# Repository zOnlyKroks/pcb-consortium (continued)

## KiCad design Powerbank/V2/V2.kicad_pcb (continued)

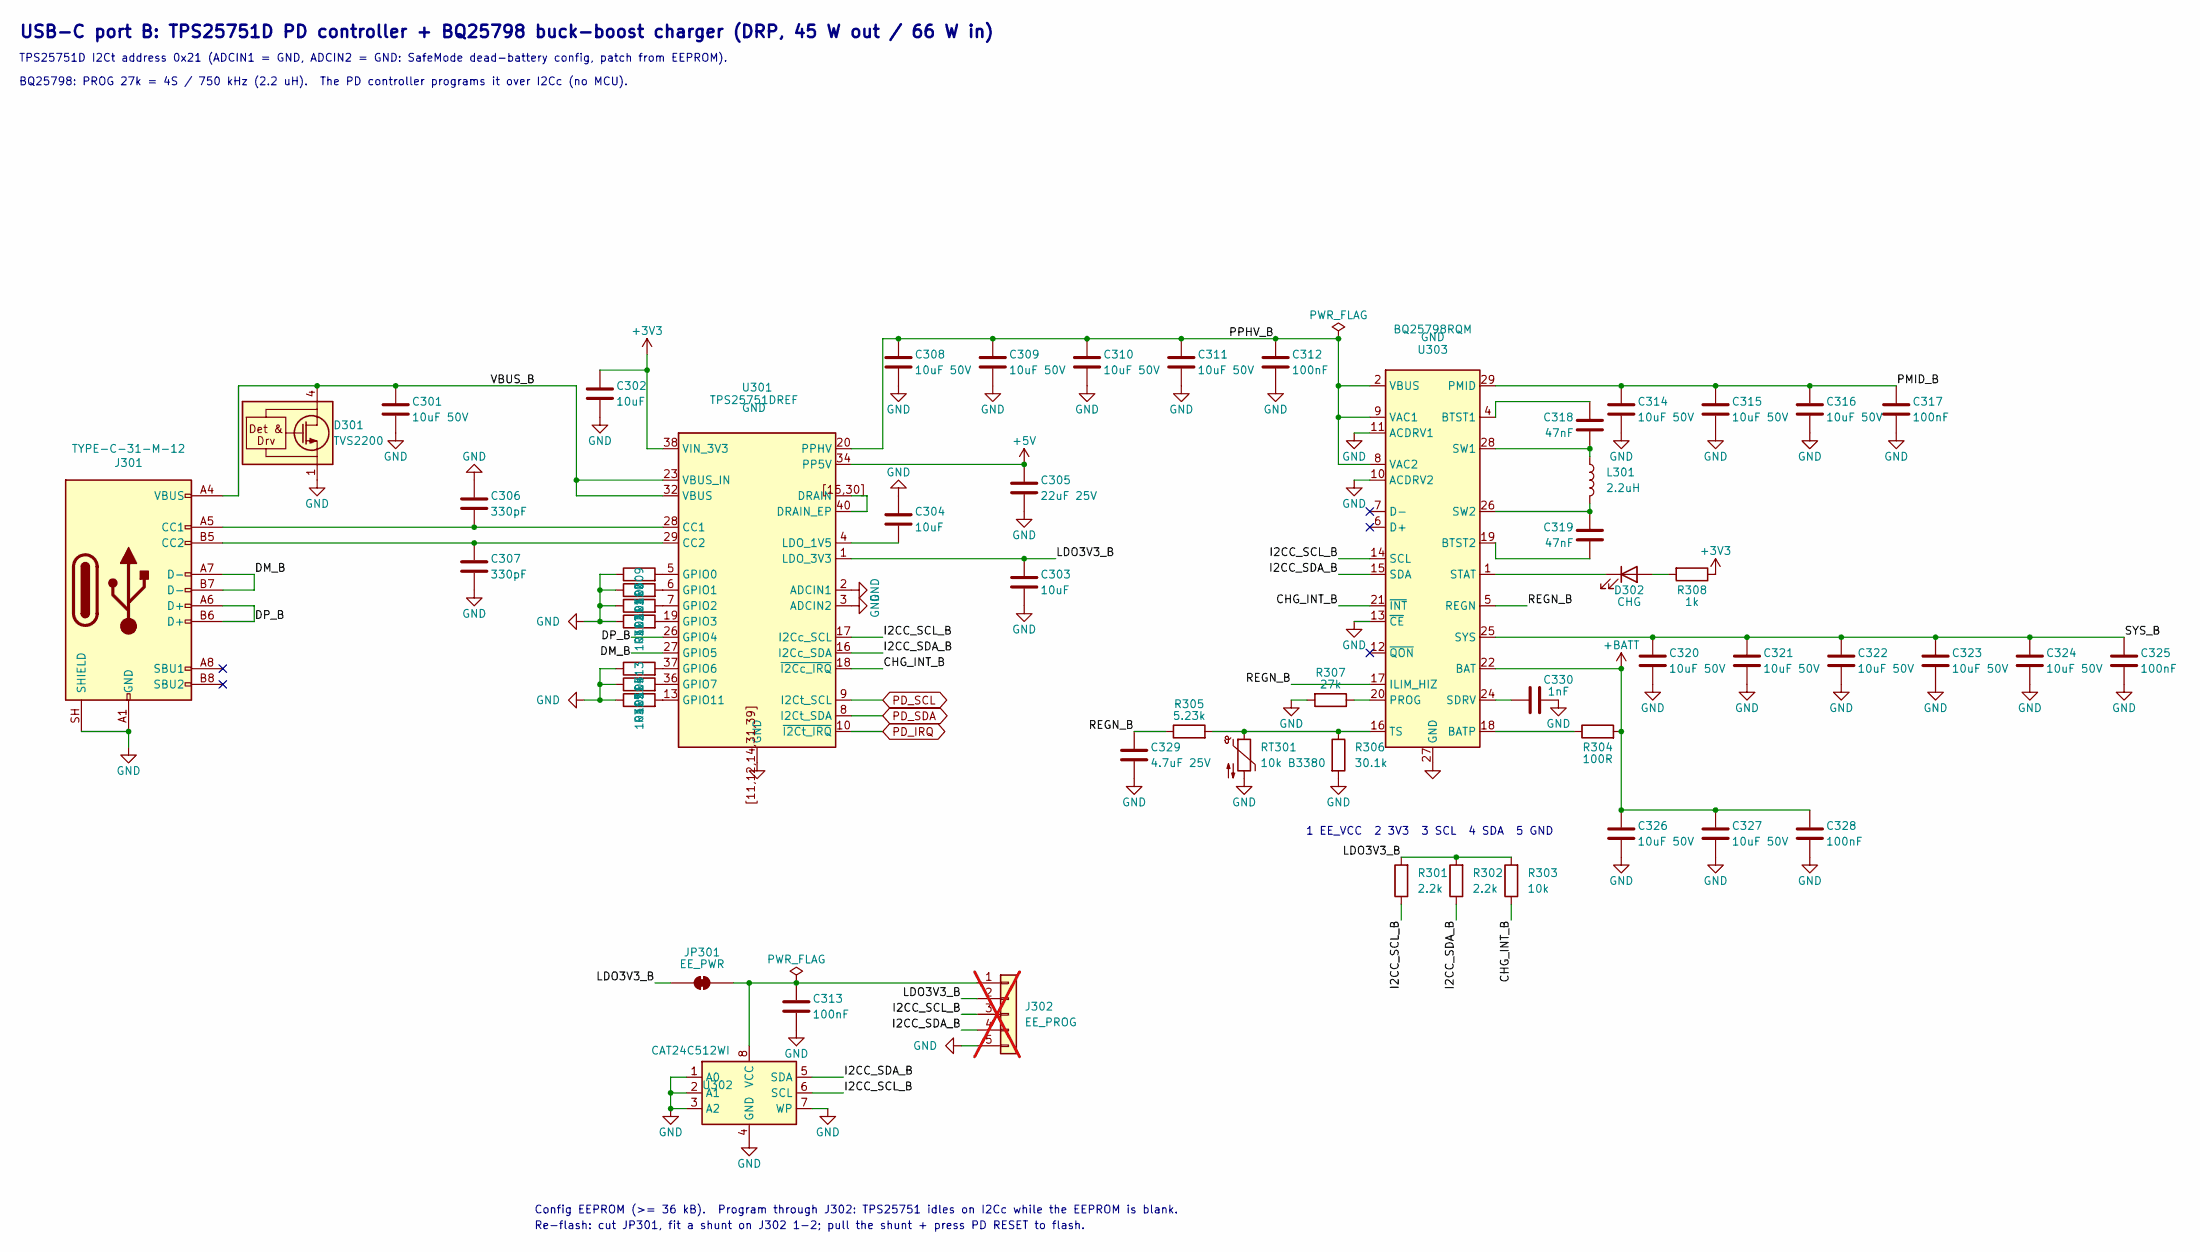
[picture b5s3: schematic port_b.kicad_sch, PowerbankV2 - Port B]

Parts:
C301, C308, C309, C310, C311, C314, C315, C316, C320, C321, C322, C323, C324, C326, C327: 10uF 50V; C_1206_3216Metric; LCSC Part # C13585
C302, C303, C304: 10uF; C_0603_1608Metric; LCSC Part # C19702
C305: 22uF 25V; C_0805_2012Metric; LCSC Part # C45783
C306, C307: 330pF; C_0603_1608Metric; LCSC Part # C1664
C312, C313, C317, C325, C328: 100nF; C_0603_1608Metric; LCSC Part # C14663
C318, C319: 47nF; C_0603_1608Metric; LCSC Part # C1622
C329: 4.7uF 25V; C_0805_2012Metric; LCSC Part # C1779
C330: 1nF; C_0603_1608Metric; LCSC Part # C1588
D301: TVS2200; WSON-6-1EP_2x2mm_P0.65mm_EP1x1.6mm; LCSC Part # C523793
D302: CHG; LED_0603_1608Metric; LCSC Part # C2286
J301: TYPE-C-31-M-12; USB_C_Receptacle_HRO_TYPE-C-31-M-12; LCSC Part # C165948
J302: EE_PROG; PinHeader_1x05_P2.54mm_Vertical; not fitted
JP301: EE_PWR; SolderJumper-2_P1.3mm_Bridged_RoundedPad1.0x1.5mm
L301: 2.2uH; L_7.0x6.6_MWSA0603S; LCSC Part # C408445
R301, R302: 2.2k; R_0603_1608Metric; LCSC Part # C4190
R303, R309, R310, R311, R312, R313, R314, R315: 10k; R_0603_1608Metric; LCSC Part # C25804
R304: 100R; R_0603_1608Metric; LCSC Part # C22775
R305: 5.23k; R_0603_1608Metric; LCSC Part # C23068
R306: 30.1k; R_0603_1608Metric; LCSC Part # C23000
R307: 27k; R_0603_1608Metric; LCSC Part # C22967
R308: 1k; R_0603_1608Metric; LCSC Part # C21190
RT301: 10k B3380; R_0603_1608Metric; LCSC Part # C13564
U301: TPS25751DREF; Texas_REF0038A_WQFN-38-2EP_6x4mm_P0.4_Via0.3; LCSC Part # C30169739
U302: CAT24C512WI; SOIC-8_3.9x4.9mm_P1.27mm; LCSC Part # C79986
U303: BQ25798RQM; Texas_RQM0029A_VQFN-29_4x4mm_P0.4mm; LCSC Part # C2876593

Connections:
+3V3: C302.1, R308.1, U301.38 (VIN_3V3); also elsewhere on the board
+5V: C305.1, U301.34 (PP5V); also elsewhere on the board
+BATT: C326.1, C327.1, C328.1, R304.2, U303.22 (BAT), U303.23 (BAT); also elsewhere on the board
/Port B/CHG_INT_B: R303.1, U301.18 (~I2Cc_IRQ), U303.21 (~INT)
/Port B/DM_B: J301.A7 (D-), J301.B7 (D-), U301.27 (GPIO5)
/Port B/DP_B: J301.A6 (D+), J301.B6 (D+), U301.26 (GPIO4)
/Port B/I2CC_SCL_B: J302.3, R301.1, U301.17 (I2Cc_SCL), U302.6 (SCL), U303.14 (SCL)
/Port B/I2CC_SDA_B: J302.4, R302.1, U301.16 (I2Cc_SDA), U302.5 (SDA), U303.15 (SDA)
/Port B/LDO3V3_B: C303.1, J302.2, JP301.1 (A), R301.2, R302.2, R303.2, U301.1 (LDO_3V3)
/Port B/PMID_B: C314.1, C315.1, C316.1, C317.1, U303.29 (PMID)
/Port B/PPHV_B: C308.1, C309.1, C310.1, C311.1, C312.1, U301.20 (PPHV), U303.2 (VBUS), U303.3 (VBUS), U303.8 (VAC2), U303.9 (VAC1)
/Port B/REGN_B: C329.1, R305.1, U303.5 (REGN), U303.17 (ILIM_HIZ)
/Port B/SYS_B: C320.1, C321.1, C322.1, C323.1, C324.1, C325.1, U303.25 (SYS)
/Port B/VBUS_B: C301.1, D301.4 (IN), D301.5 (IN), D301.6 (IN), J301.A4 (VBUS), J301.A9 (VBUS), J301.B4 (VBUS), J301.B9 (VBUS), U301.23 (VBUS_IN), U301.32 (VBUS)
GND: C301.2, C302.2, C303.2, C304.2, C305.2, C306.2, C307.2, C308.2, C309.2, C310.2, C311.2, C312.2, C313.2, C314.2, C315.2, C316.2, C317.2, C320.2, C321.2, C322.2, C323.2, C324.2, C325.2, C326.2, C327.2, C328.2, C329.2, C330.2, D301.1 (GND), D301.2 (GND), D301.3 (GND), D301.7 (GND), J301.A1 (GND), J301.A12 (GND), J301.B1 (GND), J301.B12 (GND), J301.SH (SHIELD), J302.5, R306.2, R307.2, R309.1, R310.1, R311.1, R312.1, R313.1, R314.1, R315.1, RT301.2, U301.2 (ADCIN1), U301.3 (ADCIN2), U301.11, U301.12, U301.14, U301.31, U301.39, U301.[11,12,14,31,39] (GND), U302.1 (A0), U302.2 (A1), U302.3 (A2), U302.4 (GND), U302.7 (WP), U303.10 (ACDRV2), U303.11 (ACDRV1), U303.13 (~CE), U303.27 (GND); also elsewhere on the board
unnamed: D302.2 (A), R308.2
unnamed: D302.1 (K), U303.1 (STAT)
unnamed: C306.1, J301.A5 (CC1), U301.28 (CC1)
unnamed: C307.1, J301.B5 (CC2), U301.29 (CC2)
unnamed: C313.1, J302.1, JP301.2 (B), U302.8 (VCC)
unnamed: U301.15, U301.30, U301.40 (DRAIN_EP), U301.[15,30] (DRAIN)
unnamed: R309.2, U301.5 (GPIO0)
unnamed: R310.2, U301.6 (GPIO1)
unnamed: R311.2, U301.7 (GPIO2)
unnamed: R312.2, U301.19 (GPIO3)
unnamed: R313.2, U301.37 (GPIO6)
unnamed: R314.2, U301.36 (GPIO7)
unnamed: R315.2, U301.13 (GPIO11)
unnamed: C304.1, U301.4 (LDO_1V5)
unnamed: R304.1, U303.18 (BATP)
unnamed: C318.1, U303.4 (BTST1)
unnamed: C319.1, U303.19 (BTST2)
unnamed: R307.1, U303.20 (PROG)
unnamed: C330.1, U303.24 (SDRV)
unnamed: C318.2, L301.1, U303.28 (SW1)
unnamed: C319.2, L301.2, U303.26 (SW2)
unnamed: R305.2, R306.1, RT301.1, U303.16 (TS)
PD_IRQ: U301.10 (~I2Ct_IRQ); also elsewhere on the board
PD_SCL: U301.9 (I2Ct_SCL); also elsewhere on the board
PD_SDA: U301.8 (I2Ct_SDA); also elsewhere on the board

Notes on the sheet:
Re-flash: cut JP301, fit a shunt on J302 1-2; pull the shunt + press PD RESET to flash.
1 EE_VCC 2 3V3 3 SCL 4 SDA 5 GND
USB-C port B: TPS25751D PD controller + BQ25798 buck-boost charger (DRP, 45 W out / 66 W in)
TPS25751D I2Ct address 0x21 (ADCIN1 = GND, ADCIN2 = GND: SafeMode dead-battery config, patch from EEPROM).
Config EEPROM (>= 36 kB). Program through J302: TPS25751 idles on I2Cc while the EEPROM is blank.
BQ25798: PROG 27k = 4S / 750 kHz (2.2 uH). The PD controller programs it over I2Cc (no MCU).

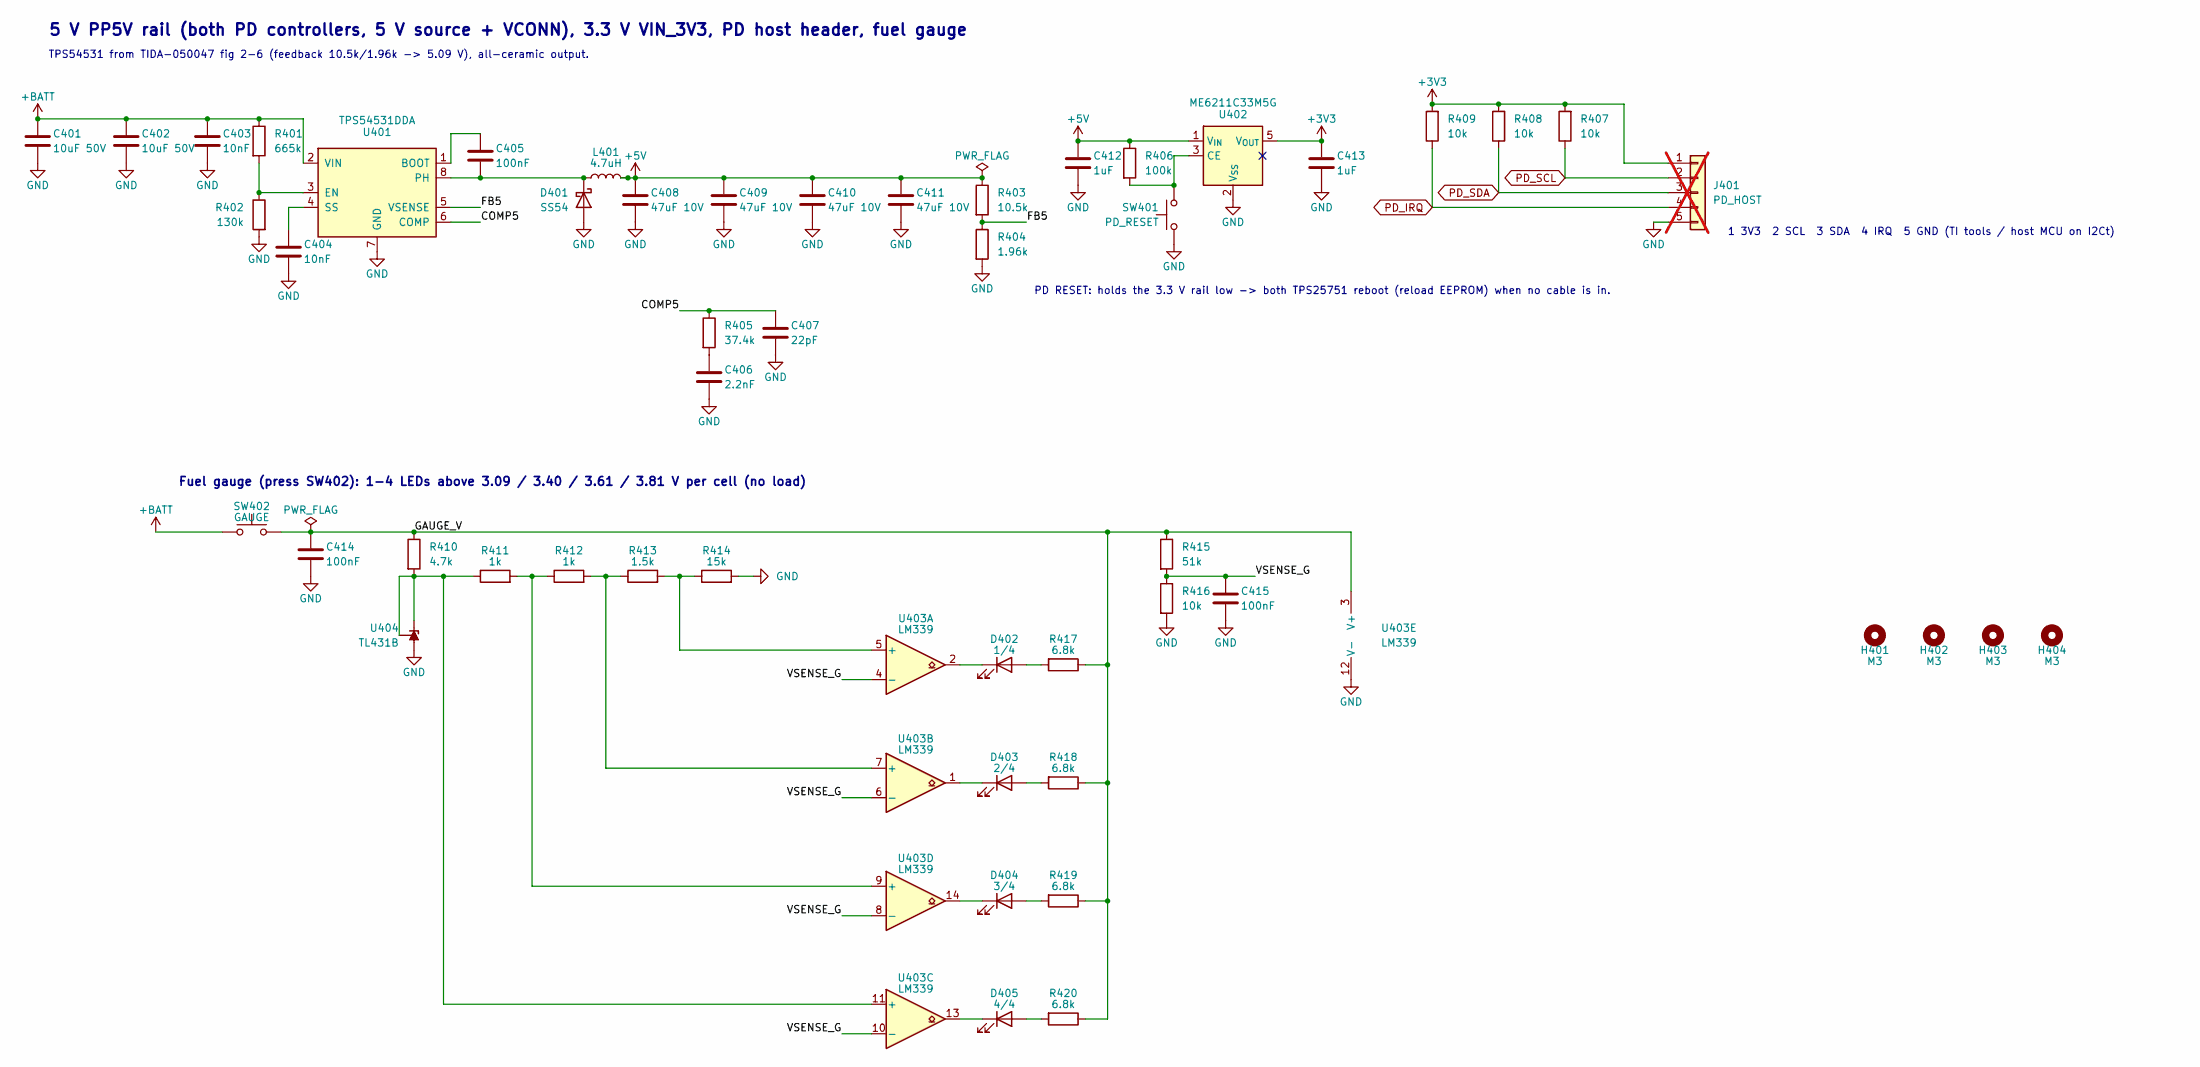
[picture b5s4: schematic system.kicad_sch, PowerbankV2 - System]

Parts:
C401, C402: 10uF 50V; C_1206_3216Metric; LCSC Part # C13585
C403, C404: 10nF; C_0603_1608Metric; LCSC Part # C57112
C405, C414, C415: 100nF; C_0603_1608Metric; LCSC Part # C14663
C406: 2.2nF; C_0603_1608Metric; LCSC Part # C1604
C407: 22pF; C_0603_1608Metric; LCSC Part # C1653
C408, C409, C410, C411: 47uF 10V; C_1206_3216Metric; LCSC Part # C96123
C412, C413: 1uF; C_0603_1608Metric; LCSC Part # C15849
D401: SS54; D_SMA; LCSC Part # C22452
D402: 1/4; LED_0603_1608Metric; LCSC Part # C2290
D403: 2/4; LED_0603_1608Metric; LCSC Part # C2290
D404: 3/4; LED_0603_1608Metric; LCSC Part # C2290
D405: 4/4; LED_0603_1608Metric; LCSC Part # C2290
H401, H402, H403, H404: M3; MountingHole_3.2mm_M3
J401: PD_HOST; PinHeader_1x05_P2.54mm_Vertical; not fitted
L401: 4.7uH; L_11x10_TMPA1004S; LCSC Part # C357112
R401: 665k; R_0603_1608Metric; LCSC Part # C23227
R402: 130k; R_0603_1608Metric; LCSC Part # C22795
R403: 10.5k; R_0603_1608Metric; LCSC Part # C22855
R404: 1.96k; R_0603_1608Metric; LCSC Part # C22854
R405: 37.4k; R_0603_1608Metric; LCSC Part # C23033
R406: 100k; R_0603_1608Metric; LCSC Part # C25803
R407, R408, R409, R416: 10k; R_0603_1608Metric; LCSC Part # C25804
R410: 4.7k; R_0603_1608Metric; LCSC Part # C23162
R411, R412: 1k; R_0603_1608Metric; LCSC Part # C21190
R413: 1.5k; R_0603_1608Metric; LCSC Part # C22843
R414: 15k; R_0603_1608Metric; LCSC Part # C22809
R415: 51k; R_0603_1608Metric; LCSC Part # C23196
R417, R418, R419, R420: 6.8k; R_0603_1608Metric; LCSC Part # C23212
SW401: PD_RESET; SW_TS-1187A_5.1x5.1; LCSC Part # C318884
SW402: GAUGE; SW_TS-1187A_5.1x5.1; LCSC Part # C318884
U401: TPS54531DDA; TI_SO-PowerPAD-8_ThermalVias; LCSC Part # C50605
U402: ME6211C33M5G; SOT-23-5; LCSC Part # C82942
U403: LM339; SOIC-14_3.9x8.7mm_P1.27mm; LCSC Part # C7948
U404: TL431B; SOT-23; LCSC Part # C41283

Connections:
+3V3: C413.1, J401.1, R407.2, R408.2, R409.2, U402.5 (V_{OUT}); also elsewhere on the board
+5V: C408.1, C409.1, C410.1, C411.1, C412.1, L401.2, R403.1, R406.1, U402.1 (V_{IN}); also elsewhere on the board
+BATT: C401.1, C402.1, C403.1, R401.1, SW402.1, U401.2 (VIN); also elsewhere on the board
/System/COMP5: C407.1, R405.1, U401.6 (COMP)
/System/FB5: R403.2, R404.1, U401.5 (VSENSE)
/System/GAUGE_V: C414.1, R410.1, R415.1, R417.1, R418.1, R419.1, R420.1, SW402.4 (2), U403.3 (V+)
/System/VSENSE_G: C415.1, R415.2, R416.1, U403.4 (-), U403.6 (-), U403.8 (-), U403.10 (-)
GND: C401.2, C402.2, C403.2, C404.2, C406.2, C407.2, C408.2, C409.2, C410.2, C411.2, C412.2, C413.2, C414.2, C415.2, D401.2 (A), J401.5, R402.2, R404.2, R414.2, R416.2, SW401.4 (2), U401.7 (GND), U401.9 (PAD), U402.2 (V_{SS}), U403.12 (V-), U404.3 (A); also elsewhere on the board
unnamed: C406.1, R405.2
unnamed: C405.2, D401.1 (K), L401.1, U401.8 (PH)
unnamed: D402.2 (A), R417.2
unnamed: D402.1 (K), U403.2
unnamed: D403.2 (A), R418.2
unnamed: D403.1 (K), U403.1
unnamed: D404.2 (A), R419.2
unnamed: D404.1 (K), U403.14
unnamed: D405.2 (A), R420.2
unnamed: D405.1 (K), U403.13
unnamed: C405.1, U401.1 (BOOT)
unnamed: R401.2, R402.1, U401.3 (EN)
unnamed: C404.1, U401.4 (SS)
unnamed: R406.2, SW401.1, U402.3 (CE)
unnamed: R413.2, R414.1, U403.5 (+)
unnamed: R412.2, R413.1, U403.7 (+)
unnamed: R410.2, R411.1, U403.11 (+), U404.1 (K), U404.2 (REF)
unnamed: R411.2, R412.1, U403.9 (+)
PD_IRQ: J401.4, R409.1; also elsewhere on the board
PD_SCL: J401.2, R407.1; also elsewhere on the board
PD_SDA: J401.3, R408.1; also elsewhere on the board

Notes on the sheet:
5 V PP5V rail (both PD controllers, 5 V source + VCONN), 3.3 V VIN_3V3, PD host header, fuel gauge
TPS54531 from TIDA-050047 fig 2-6 (feedback 10.5k/1.96k -> 5.09 V), all-ceramic output.
Fuel gauge (press SW402): 1-4 LEDs above 3.09 / 3.40 / 3.61 / 3.81 V per cell (no load)
PD RESET: holds the 3.3 V rail low -> both TPS25751 reboot (reload EEPROM) when no cable is in.
1 3V3 2 SCL 3 SDA 4 IRQ 5 GND (TI tools / host MCU on I2Ct)

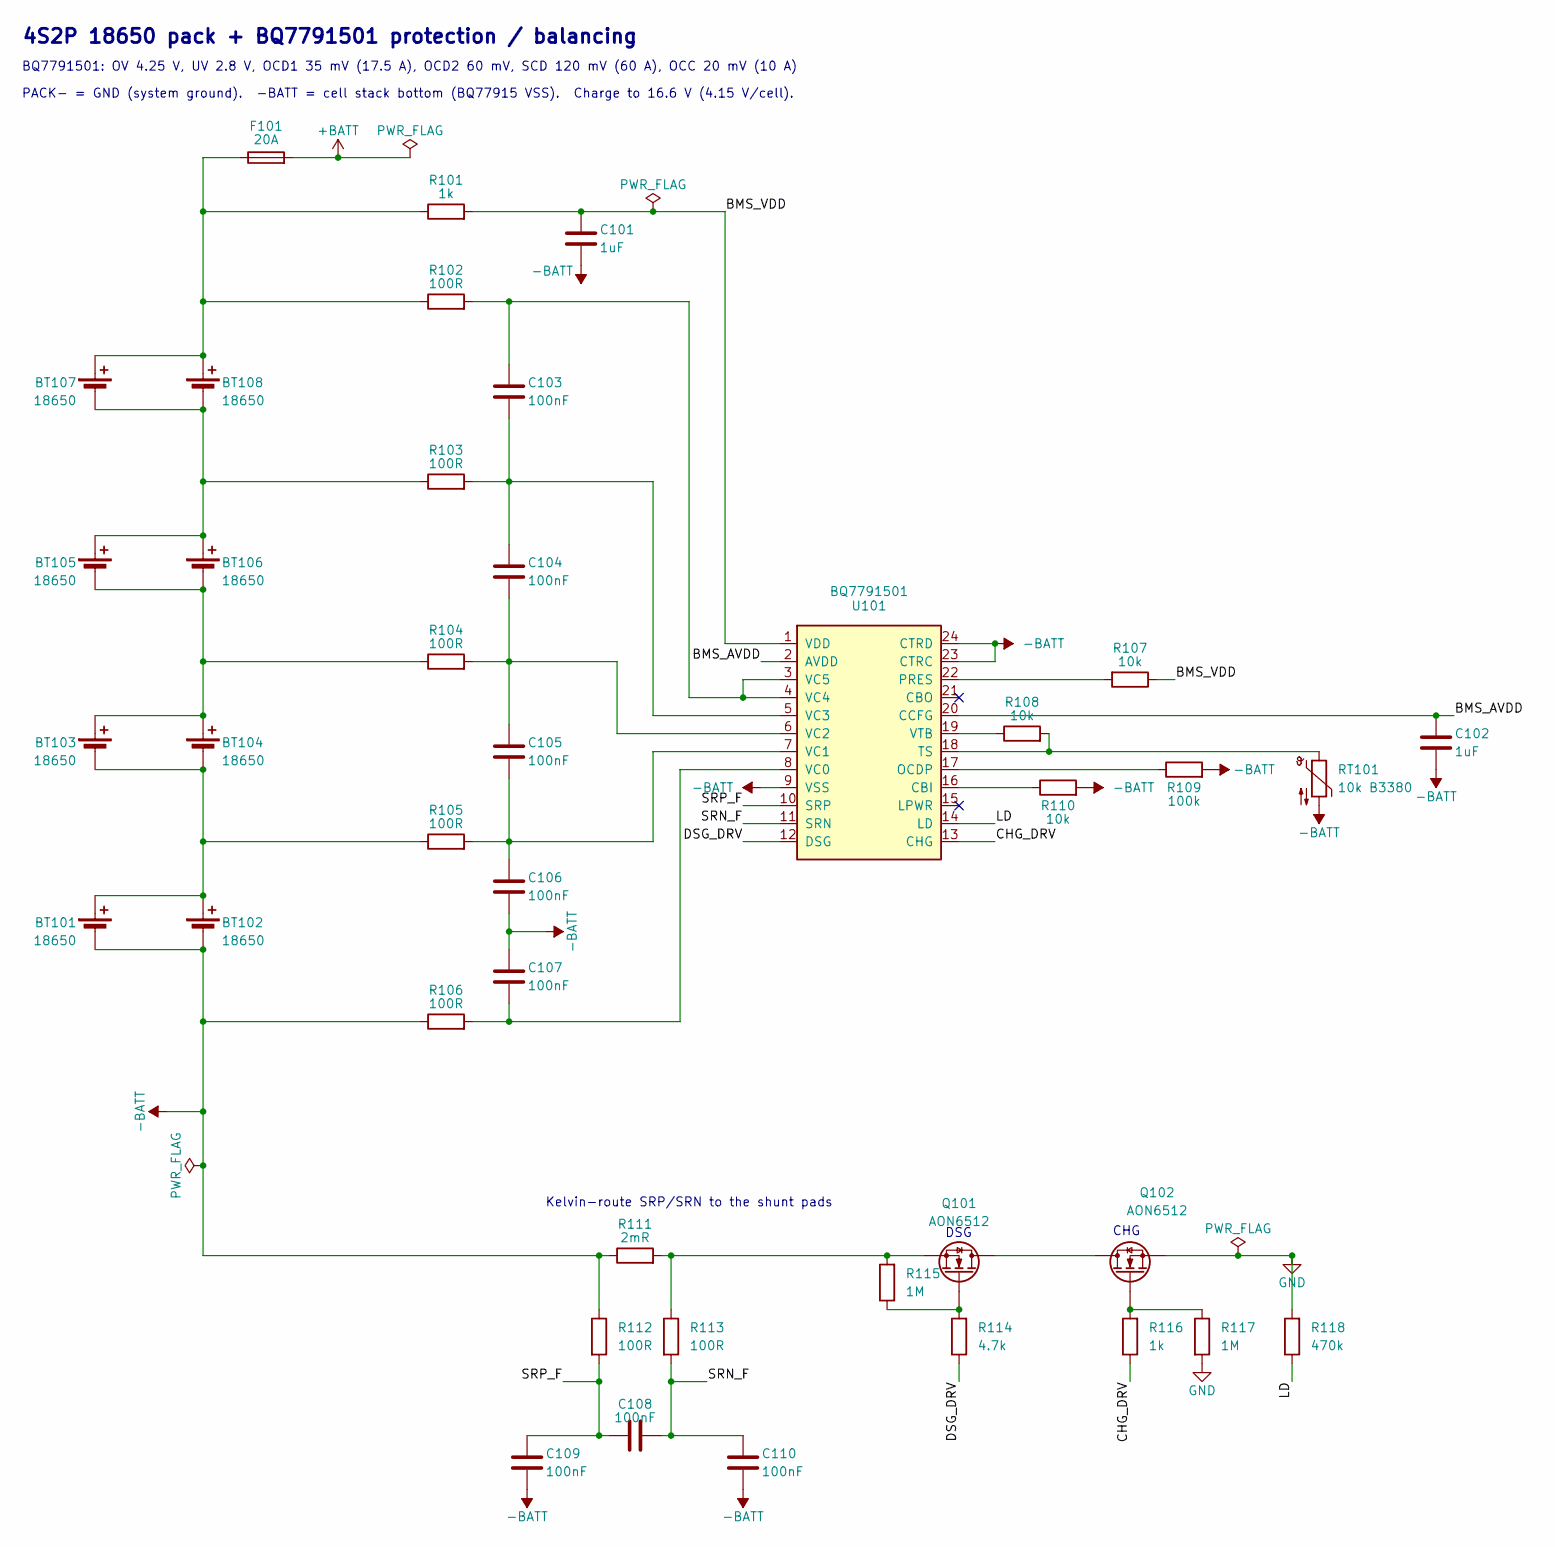
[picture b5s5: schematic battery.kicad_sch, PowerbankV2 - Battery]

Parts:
BT101, BT102, BT103, BT104, BT105, BT106, BT107, BT108: 18650; BatteryHolder_BH-18650-B1BA002; LCSC Part # C2988620
C101, C102: 1uF; C_0603_1608Metric; LCSC Part # C15849
C103, C104, C105, C106, C107, C108, C109, C110: 100nF; C_0603_1608Metric; LCSC Part # C14663
F101: 20A; Fuse_10.3x3.2_1032; LCSC Part # C5220755
Q101, Q102: AON6512; PDFN-8_5x6_AON6512; LCSC Part # C485679
R101, R116: 1k; R_0603_1608Metric; LCSC Part # C21190
R102, R103, R104, R105, R106, R112, R113: 100R; R_0603_1608Metric; LCSC Part # C22775
R107, R108, R110: 10k; R_0603_1608Metric; LCSC Part # C25804
R109: 100k; R_0603_1608Metric; LCSC Part # C25803
R111: 2mR; R_2512_6332Metric; LCSC Part # C160590
R114: 4.7k; R_0603_1608Metric; LCSC Part # C23162
R115, R117: 1M; R_0603_1608Metric; LCSC Part # C22935
R118: 470k; R_0603_1608Metric; LCSC Part # C23178
RT101: 10k B3380; R_0603_1608Metric; LCSC Part # C13564
U101: BQ7791501; TSSOP-24_4.4x7.8mm_P0.65mm; LCSC Part # C2876947

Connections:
+BATT: F101.2; also elsewhere on the board
-BATT: BT101.2 (-), BT102.2 (-), C101.2, C102.2, C106.2, C107.1, C109.2, C110.2, R106.1, R109.2, R110.2, R111.1, R112.1, RT101.2, U101.9 (VSS), U101.23 (CTRC), U101.24 (CTRD)
/Battery/BMS_AVDD: C102.1, U101.2 (AVDD), U101.20 (CCFG)
/Battery/BMS_VDD: C101.1, R101.2, R107.1, U101.1 (VDD)
/Battery/CHG_DRV: R116.1, U101.13 (CHG)
/Battery/DSG_DRV: R114.1, U101.12 (DSG)
/Battery/LD: R118.1, U101.14 (LD)
/Battery/SRN_F: C108.2, C110.1, R113.2, U101.11 (SRN)
/Battery/SRP_F: C108.1, C109.1, R112.2, U101.10 (SRP)
GND: Q102.1 (S), Q102.2 (S), Q102.3 (S), R117.2, R118.2; also elsewhere on the board
unnamed: BT101.1 (+), BT102.1 (+), BT103.2 (-), BT104.2 (-), R105.1
unnamed: BT103.1 (+), BT104.1 (+), BT105.2 (-), BT106.2 (-), R104.1
unnamed: BT105.1 (+), BT106.1 (+), BT107.2 (-), BT108.2 (-), R103.1
unnamed: BT107.1 (+), BT108.1 (+), F101.1, R101.1, R102.1
unnamed: Q101.5 (D), Q101.6 (D), Q101.7 (D), Q101.8 (D), Q101.9 (D), Q102.5 (D), Q102.6 (D), Q102.7 (D), Q102.8 (D), Q102.9 (D)
unnamed: Q101.4 (G), R114.2, R115.1
unnamed: Q101.1 (S), Q101.2 (S), Q101.3 (S), R111.2, R113.1, R115.2
unnamed: Q102.4 (G), R116.2, R117.1
unnamed: R110.1, U101.16 (CBI)
unnamed: R109.1, U101.17 (OCDP)
unnamed: R107.2, U101.22 (PRES)
unnamed: R108.2, RT101.1, U101.18 (TS)
unnamed: C107.2, R106.2, U101.8 (VC0)
unnamed: C105.2, C106.1, R105.2, U101.7 (VC1)
unnamed: C104.2, C105.1, R104.2, U101.6 (VC2)
unnamed: C103.2, C104.1, R103.2, U101.5 (VC3)
unnamed: C103.1, R102.2, U101.3 (VC5), U101.4 (VC4)
unnamed: R108.1, U101.19 (VTB)

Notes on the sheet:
4S2P 18650 pack + BQ7791501 protection / balancing
DSG
Kelvin-route SRP/SRN to the shunt pads
BQ7791501: OV 4.25 V, UV 2.8 V, OCD1 35 mV (17.5 A), OCD2 60 mV, SCD 120 mV (60 A), OCC 20 mV (10 A)
CHG
PACK- = GND (system ground). -BATT = cell stack bottom (BQ77915 VSS). Charge to 16.6 V (4.15 V/cell).

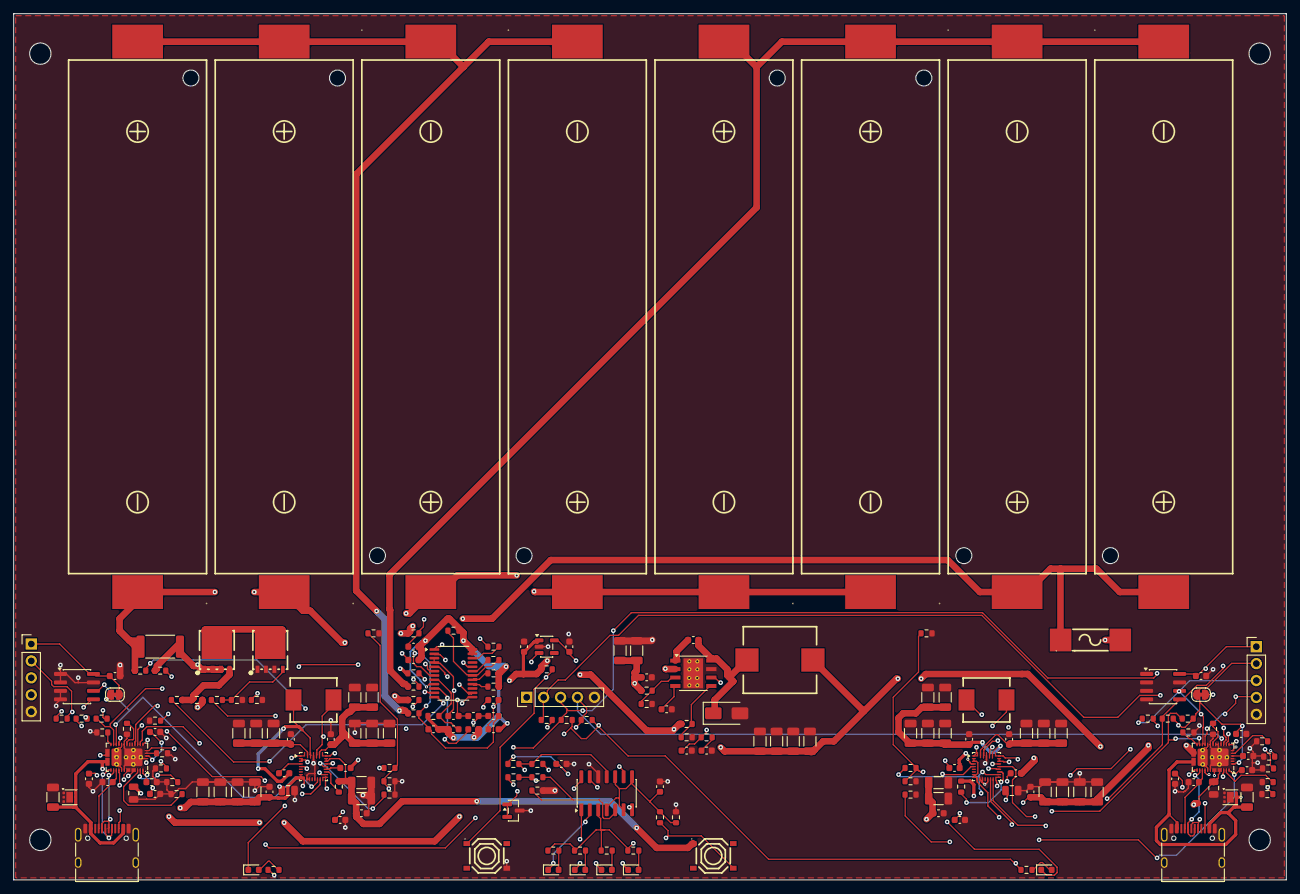
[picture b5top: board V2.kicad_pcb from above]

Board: 4 copper layers, 191.0 x 130.0 mm, 203 parts (0 on the bottom side), 121 nets.

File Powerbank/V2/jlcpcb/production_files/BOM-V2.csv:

Comment,Designator,Footprint,LCSC,Quantity
1.5k,R413,R_0603_1608Metric,C22843,1
1.96k,R404,R_0603_1608Metric,C22854,1
1/4,D402,LED_0603_1608Metric,C2290,1
10.5k,R403,R_0603_1608Metric,C22855,1
100R,"R102,R103,R104,R105,R106,R112,R113,R204,R304",R_0603_1608Metric,C22775,9
100k,"R109,R406",R_0603_1608Metric,C25803,2
100nF,"C103,C104,C105,C106,C107,C108,C109,C110,C212,C213,C217,C225,C228,C312,C313,C317,C325,C328,C405,C414,C415",C_0603_1608Metric,C14663,21
10k,"R107,R108,R110,R203,R209,R210,R211,R212,R213,R214,R215,R303,R309,R310,R311,R312,R313,R314,R315,R407,R408,R409,R416",R_0603_1608Metric,C25804,23
10k B3380,"RT101,RT201,RT301",R_0603_1608Metric,C13564,3
10nF,"C403,C404",C_0603_1608Metric,C57112,2
10uF,"C202,C203,C204,C302,C303,C304",C_0603_1608Metric,C19702,6
10uF 50V,"C201,C208,C209,C210,C211,C214,C215,C216,C220,C221,C222,C223,C224,C226,C227,C301,C308,C309,C310,C311,C314,C315,C316,C320,C321,C322,C323,C324,C326,C327,C401,C402",C_1206_3216Metric,C13585,32
130k,R402,R_0603_1608Metric,C22795,1
15k,R414,R_0603_1608Metric,C22809,1
18650,"BT101,BT102,BT103,BT104,BT105,BT106,BT107,BT108",BatteryHolder_BH-18650-B1BA002,C2988620,8
1M,"R115,R117",R_0603_1608Metric,C22935,2
1k,"R101,R116,R208,R308,R411,R412",R_0603_1608Metric,C21190,6
1nF,"C230,C330",C_0603_1608Metric,C1588,2
1uF,"C101,C102,C412,C413",C_0603_1608Metric,C15849,4
2.2k,"R201,R202,R301,R302",R_0603_1608Metric,C4190,4
2.2nF,C406,C_0603_1608Metric,C1604,1
2.2uH,"L201,L301",L_7.0x6.6_MWSA0603S,C408445,2
2/4,D403,LED_0603_1608Metric,C2290,1
20A,F101,Fuse_10.3x3.2_1032,C5220755,1
22pF,C407,C_0603_1608Metric,C1653,1
22uF 25V,"C205,C305",C_0805_2012Metric,C45783,2
27k,"R207,R307",R_0603_1608Metric,C22967,2
2mR,R111,R_2512_6332Metric,C160590,1
3/4,D404,LED_0603_1608Metric,C2290,1
30.1k,"R206,R306",R_0603_1608Metric,C23000,2
330pF,"C206,C207,C306,C307",C_0603_1608Metric,C1664,4
37.4k,R405,R_0603_1608Metric,C23033,1
4.7k,"R114,R410",R_0603_1608Metric,C23162,2
4.7uF 25V,"C229,C329",C_0805_2012Metric,C1779,2
4.7uH,L401,L_11x10_TMPA1004S,C357112,1
4/4,D405,LED_0603_1608Metric,C2290,1
470k,R118,R_0603_1608Metric,C23178,1
47nF,"C218,C219,C318,C319",C_0603_1608Metric,C1622,4
47uF 10V,"C408,C409,C410,C411",C_1206_3216Metric,C96123,4
5.23k,"R205,R305",R_0603_1608Metric,C23068,2
51k,R415,R_0603_1608Metric,C23196,1
6.8k,"R417,R418,R419,R420",R_0603_1608Metric,C23212,4
665k,R401,R_0603_1608Metric,C23227,1
AON6512,"Q101,Q102",PDFN-8_5x6_AON6512,C485679,2
BQ25798RQM,"U203,U303",Texas_RQM0029A_VQFN-29_4x4mm_P0.4mm,C2876593,2
BQ7791501,U101,TSSOP-24_4.4x7.8mm_P0.65mm,C2876947,1
CAT24C512WI,"U202,U302",SOIC-8_3.9x4.9mm_P1.27mm,C79986,2
CHG,"D202,D302",LED_0603_1608Metric,C2286,2
GAUGE,SW402,SW_TS-1187A_5.1x5.1,C318884,1
LM339,U403,SOIC-14_3.9x8.7mm_P1.27mm,C7948,1
ME6211C33M5G,U402,SOT-23-5,C82942,1
PD_RESET,SW401,SW_TS-1187A_5.1x5.1,C318884,1
SS54,D401,D_SMA,C22452,1
TL431B,U404,SOT-23,C41283,1
TPS25751DREF,"U201,U301",Texas_REF0038A_WQFN-38-2EP_6x4mm_P0.4_Via0.3,C30169739,2
TPS54531DDA,U401,TI_SO-PowerPAD-8_ThermalVias,C50605,1
TVS2200,"D201,D301",WSON-6-1EP_2x2mm_P0.65mm_EP1x1.6mm,C523793,2
TYPE-C-31-M-12,"J201,J301",USB_C_Receptacle_HRO_TYPE-C-31-M-12,C165948,2

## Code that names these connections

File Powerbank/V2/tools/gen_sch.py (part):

"""Generate the PowerbankV2 schematic (root + battery, port A, port B, system) with explicit placement and real wires.

Power symbols: +BATT = VBAT (pack + after the fuse), -BATT = BATN (cell stack bottom, BQ77915 VSS),
GND = PACK- (system ground), +5V, +3V3.  Global labels only for nets that cross sheets (PD_SCL/SDA/IRQ).
Local labels where a net has to jump inside a sheet.  Run check_netlist.py afterwards.
"""
import os, sys
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    sh.wire((XB, 38.1), "R101.1")
    sh.wire("R101.2", (119.38, 38.1))
    decap(sh, "C101", "1uF", 99.06, 38.1, gnd="-BATT")
    sh.label("BMS_VDD", (119.38, 38.1))
    sh.power("FLAG", (109.22, 38.1))

    # ---- sense inputs: RIN, CIN ladder, channels to the IC
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    flag_bat(sh, (93.98, 139.7))

    # ---- left lower pins: VSS, SRP, SRN, DSG
    for pin, name in (("U101.10", "SRP_F"), ("U101.11", "SRN_F"), ("U101.12", "DSG_DRV")):
        sh.label(name, sh.stub(pin, -5.08, 0), 180)
    p = sh.stub("U101.9", -2.54, 0)
    sh.power("-BATT", p, rot=90)
    # AVDD -> label, cap on the right with CCFG
    sh.label("BMS_AVDD", sh.stub("U101.2", -2.54, 0), 180)

    # ---- right side
    RX = UX + 12.7
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    sh.power("-BATT", (RX + 5.08, sh.P("U101.24")[1]), rot=270)
    hR(sh, "R107", "10k", RX + 2.54, sh.P("U101.22")[1], flip=True)    # PRES pull-up to BMS_VDD
    sh.wire("U101.22", "R107.2")
    sh.label("BMS_VDD", sh.stub("R107.1", 2.54, 0))
    sh.nc("U101.21")
    sh.nc("U101.15")
    p = sh.stub("U101.20", 50.8, 0)                                     # CCFG -> AVDD (4-cell)
    sh.label("BMS_AVDD", p)
    vC(sh, "C102", "1uF", p[0] - 2.54, p[1])
    sh.power("-BATT", "C102.2", rot=180)
    yv, yt = sh.P("U101.19")[1], sh.P("U101.18")[1]
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        sh.wire(pin, ref + ".1")
        sh.power("-BATT", sh.stub(ref + ".2", 2.54, 0), rot=270)
    sh.label("LD", sh.stub("U101.14", 5.08, 0))
    sh.label("CHG_DRV", sh.stub("U101.13", 5.08, 0))

    # ---- shunt, sense filter, FETs (bottom row y = 185.42)
    YB = 185.42
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    # gate networks
    gq1, gq2 = sh.P("Q101.4"), sh.P("Q102.4")
    vR(sh, "R114", "4.7k", gq1[0], gq1[1], flip=True)                   # pin 2 (gate) on top
    sh.label("DSG_DRV", sh.stub("R114.1", 0, 2.54), 270)
    vR(sh, "R115", "1M", gq1[0] - 10.16, YB, flip=True)                 # SNS_N (pin 2) on top
    sh.wire(gq1, "R115.1")
    vR(sh, "R116", "1k", gq2[0], gq2[1], flip=True)
    sh.label("CHG_DRV", sh.stub("R116.1", 0, 2.54), 270)
    vR(sh, "R117", "1M", gq2[0] + 10.16, gq2[1])
    sh.wire(gq2, "R117.1")
    sh.power("GND", "R117.2")
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    hC(sh, "C108", "100nF", xs + 1.27, yf + 7.62)
    sh.wire((xs, yf), (xs, yf + 7.62), "C108.1")
    sh.wire("C108.2", (xs + 10.16, yf + 7.62), (xs + 10.16, yf))
    sh.label("SRP_F", sh.stub((xs, yf), -5.08, 0), 180)
    sh.label("SRN_F", sh.stub((xs + 10.16, yf), 5.08, 0))
    vC(sh, "C109", "100nF", xs - 10.16, yf + 7.62)
    sh.wire((xs, yf + 7.62), (xs - 10.16, yf + 7.62))
    flag_bat(sh, "C109.2")
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    sh.label(SCL, sh.stub(U + ".17", 5.08, 0))
    sh.label(SDA, sh.stub(U + ".16", 5.08, 0))
    sh.label(INT, sh.stub(U + ".18", 5.08, 0))
    sh.glabel("PD_SCL", sh.stub(U + ".9", 5.08, 0))
    sh.glabel("PD_SDA", sh.stub(U + ".8", 5.08, 0))
    sh.glabel("PD_IRQ", sh.stub(U + ".10", 5.08, 0))
    sh.power("GND", U + ".[11,12,14,31,39]")

    # ---------------------------------------------------------------- EEPROM, jumper, programming header, pull-ups
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    sh.label(SDA, sh.stub(Q + ".15", -5.08, 0), 180)
    sh.label(INT, sh.stub(Q + ".21", -5.08, 0), 180)
    sh.power("GND", sh.stub(Q + ".13", -2.54, 0))
    sh.label(REGN, sh.stub(Q + ".17", -5.08, 0), 180)
    hR(sh, "R" + r(7), "27k", 228.6, 127.0, flip=True)                  # PROG (pin 1) on the right
    sh.wire("R%s.1" % r(7), Q + ".20")
    sh.power("GND", sh.stub("R%s.2" % r(7), -2.54, 0))
    sh.wire(Q + ".16", (213.36, 132.08))
    hR(sh, "R" + r(5), "5.23k", 205.74, 132.08)
    sh.wire("R%s.1" % r(5), (200.66, 132.08))
    sh.label(REGN, (200.66, 132.08), 180)
    decap(sh, "C" + r(29), "4.7uF 25V", 200.66, 132.08)
    vR(sh, "R" + r(6), "30.1k", 233.68, 132.08)
    sh.power("GND", "R%s.2" % r(6))
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    hR(sh, "R" + r(8), "1k", 276.86, 106.68, flip=True, fields="B")
    sh.wire("D%s.2" % r(2), "R%s.2" % r(8))
    sh.power("+3V3", "R%s.1" % r(8))
    sh.label(REGN, sh.stub(Q + ".5", 5.08, 0))
    sh.wire(Q + ".25", (340.36, 116.84))
    sh.label("SYS_" + sfx, (340.36, 116.84))
    for k, x in ((20, 294.64), (21, 302.26), (22, 309.88), (23, 317.5), (24, 325.12)):
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    sh.power("GND", "R404.2")
    sh.label("FB5", sh.stub((175.26, 106.68), 5.08, 0))
    sh.label("FB5", sh.stub("U401.5", 5.08, 0))
    sh.label("COMP5", sh.stub("U401.6", 5.08, 0))
    sh.wire((124.46, 121.92), (137.16, 121.92))
    sh.label("COMP5", (124.46, 121.92), 180)
    vR(sh, "R405", "37.4k", 129.54, 121.92)
    vC(sh, "C406", "2.2nF", 129.54, 129.54)
    sh.power("GND", "C406.2")
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    sh.add("J401", "Connector_Generic:Conn_01x05", 299.72, 101.6, value="PD_HOST",
           fp="Connector_PinHeader_2.54mm:PinHeader_1x05_P2.54mm_Vertical", fields="R", dnp=True)
    sh.wire((287.02, 96.52), "J401.1")
    for ref, x, pin, net in (("R407", 264.16, "J401.2", "PD_SCL"), ("R408", 259.08, "J401.3", "PD_SDA"),
                             ("R409", 254.0, "J401.4", "PD_IRQ")):
        vR(sh, ref, "10k", x, 86.36, flip=True)                             # pin 2 (+3V3) on top
        y = sh.P(pin)[1]
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           fields="T")
    sh.wire((50.8, 160.02), "SW402.1")
    sh.wire("SW402.4", (228.6, 160.02))
    sh.label("GAUGE_V", (68.58, 160.02))
    sh.power("FLAG", (66.04, 160.02))
    decap(sh, "C414", "100nF", 71.12, 160.02)
    vR(sh, "R410", "4.7k", 78.74, 160.02)
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               lcsc="C7948", fields="T", unit=unit)
        plus, minus, out = units[unit]
        sh.wire((xn, 167.64), (xn, y - 2.54), "%s.%s" % (key, plus))
        sh.label("VSENSE_G", sh.stub("%s.%s" % (key, minus), -5.08, 0), 180)
        sh.add(led, "Device:LED", 180.34, y, value="%d/4" % (i + 1), fp="LED_SMD:LED_0603_1608Metric", lcsc="C2290",
               fields="T")
        sh.wire("%s.%s" % (key, out), led + ".1")
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    sh.power("GND", "R416.2")
    sh.wire((208.28, 167.64), (215.9, 167.64))
    decap(sh, "C415", "100nF", 215.9, 167.64)
    sh.label("VSENSE_G", sh.stub((215.9, 167.64), 5.08, 0))
    # mounting holes
    for i in range(4):
        sh.add("H40%d" % (i + 1), "Mechanical:MountingHole", 330.2 + 10.16 * i, 177.8, value="M3",
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
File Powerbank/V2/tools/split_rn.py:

"""One-off edit of the hand-tidied port_a.kicad_sch: the GPIO pull-down arrays RN201 / RN202 become single 10k
0603 resistors R209-R215 (same rows, same GND rail), so each one can sit right at its TPS25751D pin on the board.

R209 GPIO0, R210 GPIO1, R211 GPIO2, R212 GPIO3 (RN201 rows), R213 GPIO6, R214 GPIO7, R215 GPIO11 (RN202 rows).
Pin 1 = GND (left, joins the old array GND rail), pin 2 = GPIO (right, on the TPS25751D pin).
Then run copy_port_layout.py for port B.
"""
import copy, os, sys, uuid
sys.path.insert(0, os.path.dirname(os.path.abspath(__file__)))
from sexp import parse, dump, find, find_all, q, unq
import schlib
from copy_port_layout import ref_of, set_prop, pin_pos

A = os.path.join(schlib.PRJ, "port_a.kicad_sch")
NS = uuid.UUID("0c1d7e55-2b6a-4f1e-8e43-91d2a7c6b5f0")
ROWS = {"RN201": [("R209", "8"), ("R210", "7"), ("R211", "6"), ("R212", "5")],
        "RN202": [("R213", "8"), ("R214", "7"), ("R215", "6")]}


def main():
    t = parse(open(A, encoding="utf-8").read())[0]
    syms = {ref_of(s): s for s in find_all(t, "symbol")}
    if "RN201" not in syms:
        raise SystemExit("already split")
    tmpl = syms["R201"]
    n = [0]

    def fresh():
        n[0] += 1
        return q(str(uuid.uuid5(NS, "split:%d" % n[0])))
    new_items = []
    for rn, rows in ROWS.items():
        s = syms[rn]
        for ref, pin in rows:
            x2, y = pin_pos(s, pin)                          # GPIO end (TPS pin)
            r = copy.deepcopy(tmpl)
            at = find(r, "at")
            at[1], at[2], at[3] = schlib.fmt(x2 - 3.81), schlib.fmt(y), "90"   # rot 90: pin 1 left, pin 2 right
            r[r.index(find(r, "uuid"))] = ["uuid", fresh()]
            for p in find_all(r, "pin"):
                p[p.index(find(p, "uuid"))] = ["uuid", fresh()]
            set_prop(r, "Reference", ref)
            set_prop(r, "Value", "10k")
            set_prop(r, "Footprint", "Resistor_SMD:R_0603_1608Metric")
            set_prop(r, "LCSC Part #", "C25804")
            for p in find_all(r, "property"):                # fields: ref above, value below, others hidden
                k = unq(p[1])
                pa = find(p, "at")
                if k == "Reference":
                    pa[1], pa[2], pa[3] = schlib.fmt(x2 - 3.81), schlib.fmt(y - 1.27), "0"
                elif k == "Value":
                    pa[1], pa[2], pa[3] = schlib.fmt(x2 - 3.81), schlib.fmt(y + 1.27), "0"
                else:
                    pa[1], pa[2] = schlib.fmt(x2 - 3.81), schlib.fmt(y)
            path = find(find(find(r, "instances"), "project"), "path")
            path[path.index(find(path, "reference"))] = ["reference", q(ref)]
            assert pin_pos(r, "2") == (x2, y), (ref, pin_pos(r, "2"))
            x1 = pin_pos(r, "1")[0]
            new_items.append(r)
            gx = pin_pos(s, {"8": "1", "7": "2", "6": "3", "5": "4"}[pin])[0]      # old GND-side pin column
            new_items.append(["wire", ["pts", ["xy", schlib.fmt(x1), schlib.fmt(y)], ["xy", schlib.fmt(gx), schlib.fmt(y)]],
                              ["stroke", ["width", "0"], ["type", "default"]], ["uuid", fresh()]])
        t.remove(s)
    # the arrays' spare pins (R4 of RN202) had no-connect flags; drop the ones that no longer sit on a pin
    pins = {pin_pos(s, num) for s in find_all(t, "symbol") + [x for x in new_items if x[0] == "symbol"]
            for num in schlib.pins_of(schlib.flat_symbol(unq(find(s, "lib_id")[1])), int(find(s, "unit")[1]))}
    for nc in find_all(t, "no_connect"):
        a = find(nc, "at")
        if (float(a[1]), float(a[2])) not in pins:
            t.remove(nc)
    # junctions where a new wire meets the GND rail between two rail segments
    ends = {}
    for w in find_all(t, "wire") + [x for x in new_items if x[0] == "wire"]:
        pts = find(w, "pts")
        for e in pts[1:3]:
            k = (float(e[1]), float(e[2]))
            ends[k] = ends.get(k, 0) + 1
    have = {(float(find(j, "at")[1]), float(find(j, "at")[2])) for j in find_all(t, "junction")}
    for k, c in ends.items():
        if c >= 3 and k not in have:
            new_items.append(["junction", ["at", schlib.fmt(k[0]), schlib.fmt(k[1])], ["diameter", "0"],
                              ["color", "0", "0", "0", "0"], ["uuid", fresh()]])
    i = t.index(find_all(t, "symbol")[0])
    for it in new_items:
        t.insert(i, it)
    open(A, "w", encoding="utf-8").write(dump(t) + "\n")
    print("port A: RN201/RN202 -> R209..R215")


if __name__ == "__main__":
    main()
